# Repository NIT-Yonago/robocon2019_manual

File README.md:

# robocon2019_manual
# 
# Arduino/
## Controller
Wiiクラシックコントローラのデータをそのまま送信する

## hanging_system
ハンガーをかける機構のプログラム

Wiiから受信して，加工したデータを足回りに送る機能も持つ

## MD_Green
モータードライバ＊３

電磁弁駆動＊３

ロボット角度補正用ジャイロ

CAN通信（未実装）
# 
# KiCad/
## wii_controller
Controllerの基板

## AIR_SRV_SIX
hanging_systemの基板

## MD_2016_remake
MD_Greenの基板

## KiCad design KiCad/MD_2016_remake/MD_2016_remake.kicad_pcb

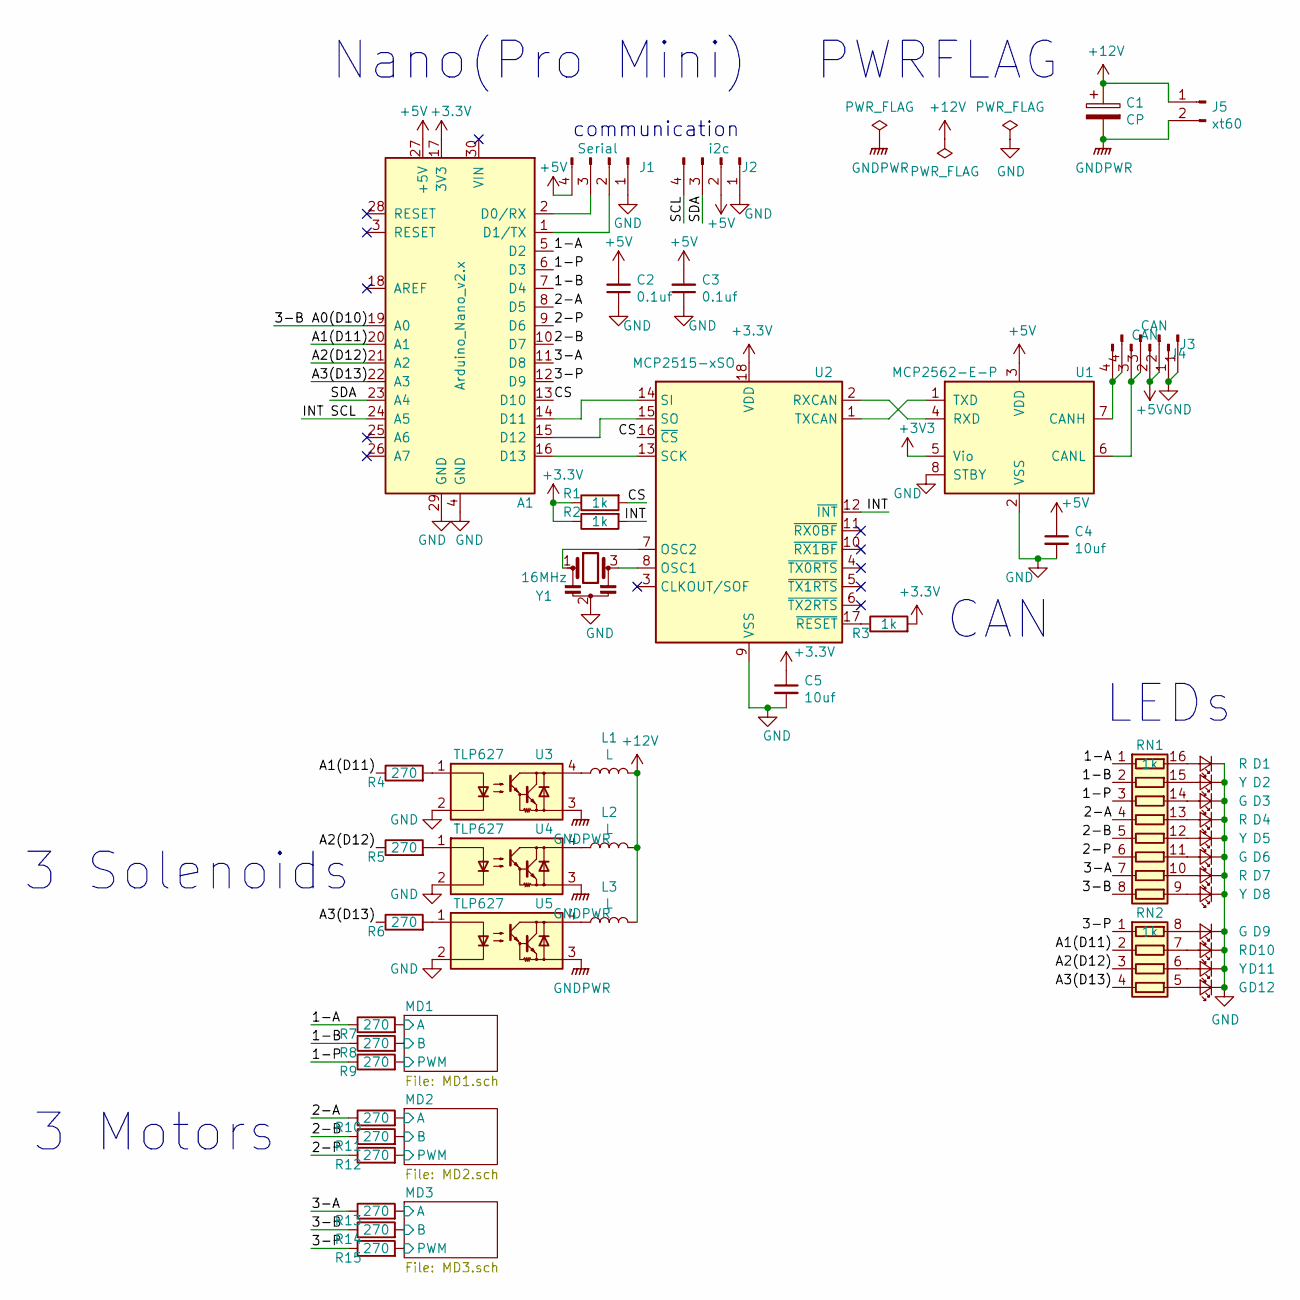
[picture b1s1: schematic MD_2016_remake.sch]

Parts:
A1: Arduino_Nano_v2.x; Arduino_Nano
C1: CP; CP_Radial_D10.0mm_P5.00mm
C2, C3: 0.1uf; C_0603_1608Metric
C4, C5: 10uf; C_0603_1608Metric
D1, D4, D7, D10: R; LED_0603_1608Metric
D2, D5, D8, D11: Y; LED_0603_1608Metric
D3, D6, D9, D12: G; LED_0603_1608Metric
J1: Serial; JST_PH_B4B-PH-K_1x04_P2.00mm_Vertical
J2: i2c; JST_PH_B4B-PH-K_1x04_P2.00mm_Vertical
J3, J4: CAN; JST_PH_B4B-PH-K_1x04_P2.00mm_Vertical
J5: xt60; XT60PT-M
L1, L2, L3: L; JST_PH_B2B-PH-K_1x02_P2.00mm_Vertical
R1, R2, R3: 1k; R_0603_1608Metric
R4, R5, R6, R7, R8, R9, R10, R11, R12, R13, R14, R15: 270; R_0603_1608Metric
RN1: 1k; R_Array_Convex_8x0602
RN2: 1k; R_Array_Convex_4x0603
U1: MCP2562-E-P; DIP-8_W7.62mm
U2: MCP2515-xSO; DIP-18_W7.62mm_Socket
U3, U4, U5: TLP627; DIP-4_W7.62mm
Y1: 16MHz; Resonator_muRata_CSTLSxxxX-3Pin_W5.5mm_H3.0mm

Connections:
+5V: A1.27 (+5V), C2.2, C3.2, C4.1, J1.4, J2.2, J3.2, J4.2, U1.3 (VDD)
+12V: C1.1, J5.1, L1.2, L2.2, L3.2; also elsewhere on the board
/1-A: A1.5 (D2), R7.1, RN1.1 (R1.1)
/1-B: A1.7 (D4), R8.1, RN1.2 (R2.1)
/1-P: A1.6 (D3), R9.1, RN1.3 (R3.1)
/2-A: A1.8 (D5), R10.1, RN1.4 (R4.1)
/2-B: A1.10 (D7), R11.1, RN1.5 (R5.1)
/2-P: A1.9 (D6), R12.1, RN1.6 (R6.1)
/3-A: A1.11 (D8), R13.1, RN1.7 (R7.1)
/3-B: A1.19 (A0), R14.1, RN1.8 (R8.1)
/3-P: A1.12 (D9), R15.1, RN2.1 (R1.1)
/A1(D11): A1.20 (A1), R4.1, RN2.2 (R2.1)
/A2(D12): A1.21 (A2), R5.1, RN2.3 (R3.1)
/A3(D13): A1.22 (A3), R6.1, RN2.4 (R4.1)
/CS: A1.13 (D10), R1.2, U2.16 (~CS)
/INT: A1.24 (A5), J2.4, R2.2, U2.12 (~INT)
/MD1/A: R7.2; also elsewhere on the board
/MD1/B: R8.2; also elsewhere on the board
/MD1/PWM: R9.2; also elsewhere on the board
/MD2/A: R10.2; also elsewhere on the board
/MD2/B: R11.2; also elsewhere on the board
/MD2/PWM: R12.2; also elsewhere on the board
/MD3/A: R13.2; also elsewhere on the board
/MD3/B: R14.2; also elsewhere on the board
/MD3/PWM: R15.2; also elsewhere on the board
/SDA: A1.23 (A4), J2.3
GND: A1.4 (GND), A1.29 (GND), C2.1, C3.1, C4.2, C5.2, D1.1 (K), D2.1 (K), D3.1 (K), D4.1 (K), D5.1 (K), D6.1 (K), D7.1 (K), D8.1 (K), D9.1 (K), D10.1 (K), D11.1 (K), D12.1 (K), J1.1, J2.1, J3.1, J4.1, U1.2 (VSS), U1.8 (STBY), U2.9 (VSS), U3.2, U4.2, U5.2, Y1.2; also elsewhere on the board
GNDPWR: C1.2, J5.2, U3.3, U4.3, U5.3; also elsewhere on the board
unnamed: A1.1 (D1/TX), J1.2
unnamed: A1.2 (D0/RX), J1.3
unnamed: A1.14 (D11), U2.14 (SI)
unnamed: A1.15 (D12), U2.15 (SO)
unnamed: A1.16 (D13), U2.13 (SCK)
unnamed: D1.2 (A), RN1.16 (R1.2)
unnamed: D2.2 (A), RN1.15 (R2.2)
unnamed: D3.2 (A), RN1.14 (R3.2)
unnamed: D4.2 (A), RN1.13 (R4.2)
unnamed: D5.2 (A), RN1.12 (R5.2)
unnamed: D6.2 (A), RN1.11 (R6.2)
unnamed: D7.2 (A), RN1.10 (R7.2)
unnamed: D8.2 (A), RN1.9 (R8.2)
unnamed: D9.2 (A), RN2.8 (R1.2)
unnamed: D10.2 (A), RN2.7 (R2.2)
unnamed: D11.2 (A), RN2.6 (R3.2)
unnamed: D12.2 (A), RN2.5 (R4.2)
unnamed: J3.3, J4.3, U1.6 (CANL)
unnamed: J3.4, J4.4, U1.7 (CANH)
unnamed: L1.1, U3.4
unnamed: L2.1, U4.4
unnamed: L3.1, U5.4
unnamed: R3.1, U2.17 (~RESET)
unnamed: R4.2, U3.1
unnamed: R5.2, U4.1
unnamed: R6.2, U5.1
unnamed: U1.1 (TXD), U2.1 (TXCAN)
unnamed: U1.4 (RXD), U2.2 (RXCAN)
unnamed: U2.7 (OSC2), Y1.1
unnamed: U2.8 (OSC1), Y1.3

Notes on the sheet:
3 Motors
CAN
Nano(Pro Mini)
PWRFLAG
communication
LEDs
3 Solenoids

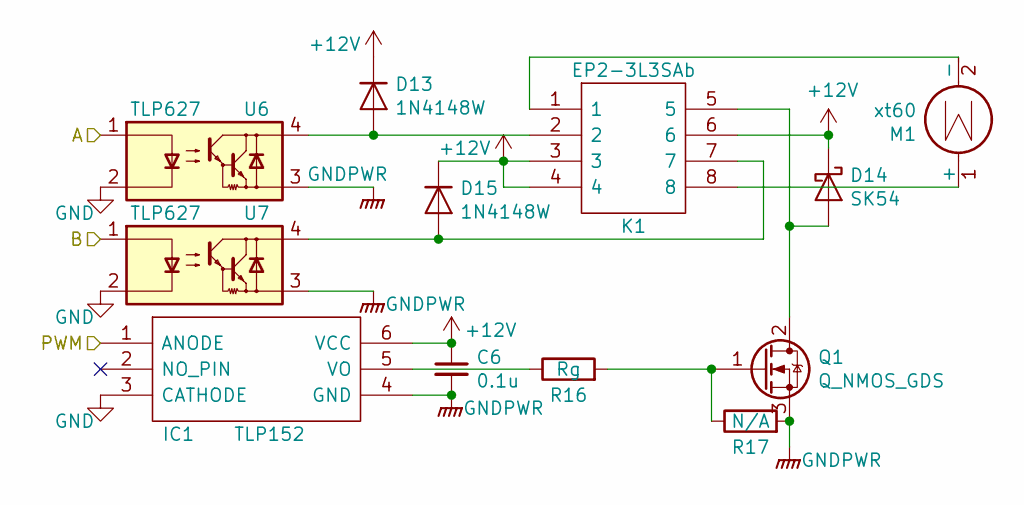
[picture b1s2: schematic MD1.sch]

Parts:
C6: 0.1u; C_0603_1608Metric
D13, D15: 1N4148W; D_SOD-123
D14: SK54; D_SMC
IC1: TLP152; SO-5_4.4x3.6mm_P1.27mm; Manufacturer_Part_Number TLP152(E(T
K1: EP2-3L3SAb; EP2_H-BRIDGE; Manufacturer_Part_Number EP2-3L3SAb
M1: xt60; XT60PT-F
Q1: Q_NMOS_GDS; TO-247-3_Vertical
R16: Rg; R_0603_1608Metric_Pad1.05x0.95mm_HandSolder
R17: N/A; R_0603_1608Metric_Pad1.05x0.95mm_HandSolder
U6, U7: TLP627; DIP-4_W7.62mm

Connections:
+12V: C6.1, D13.1 (K), D14.1 (K), D15.1 (K), IC1.6 (VCC), K1.3, K1.4, K1.6; also elsewhere on the board
/MD1/A: U6.1; also elsewhere on the board
/MD1/B: U7.1; also elsewhere on the board
/MD1/PWM: IC1.1 (ANODE); also elsewhere on the board
GND: IC1.3 (CATHODE), U6.2, U7.2; also elsewhere on the board
GNDPWR: C6.2, IC1.4 (GND), Q1.3 (S), R17.2, U6.3, U7.3; also elsewhere on the board
unnamed: D13.2 (A), K1.2, U6.4
unnamed: D14.2 (A), K1.5, Q1.2 (D)
unnamed: D15.2 (A), K1.7, U7.4
unnamed: IC1.5 (VO), R16.1
unnamed: K1.1, M1.2 (-)
unnamed: K1.8, M1.1 (+)
unnamed: Q1.1 (G), R16.2, R17.1

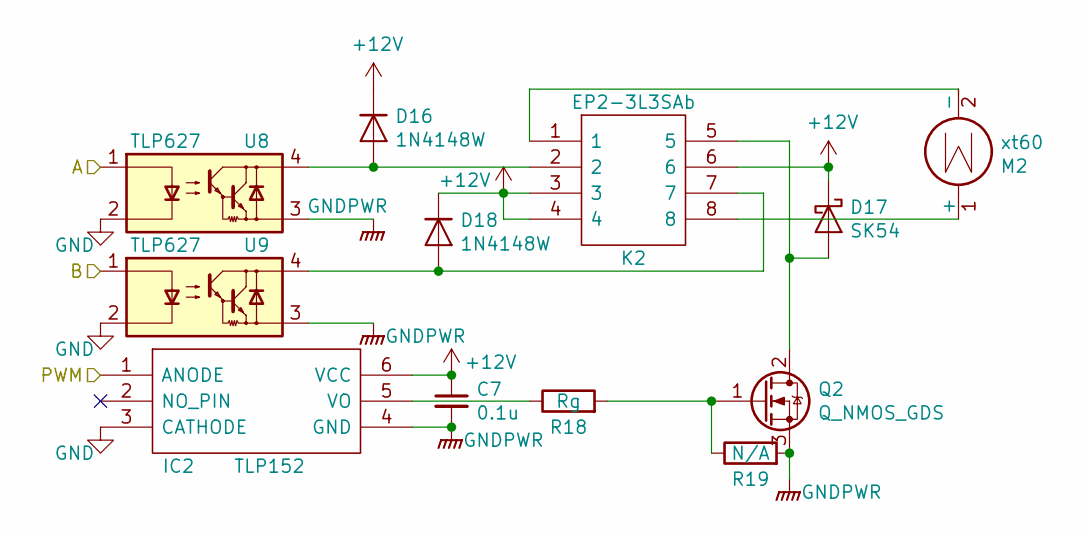
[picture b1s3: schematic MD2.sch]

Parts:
C7: 0.1u; C_0603_1608Metric
D16, D18: 1N4148W; D_SOD-123
D17: SK54; D_SMC
IC2: TLP152; SO-5_4.4x3.6mm_P1.27mm; Manufacturer_Part_Number TLP152(E(T
K2: EP2-3L3SAb; EP2_H-BRIDGE; Manufacturer_Part_Number EP2-3L3SAb
M2: xt60; XT60PT-F
Q2: Q_NMOS_GDS; TO-247-3_Vertical
R18: Rg; R_0603_1608Metric_Pad1.05x0.95mm_HandSolder
R19: N/A; R_0603_1608Metric_Pad1.05x0.95mm_HandSolder
U8, U9: TLP627; DIP-4_W7.62mm

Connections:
+12V: C7.1, D16.1 (K), D17.1 (K), D18.1 (K), IC2.6 (VCC), K2.3, K2.4, K2.6; also elsewhere on the board
/MD2/A: U8.1; also elsewhere on the board
/MD2/B: U9.1; also elsewhere on the board
/MD2/PWM: IC2.1 (ANODE); also elsewhere on the board
GND: IC2.3 (CATHODE), U8.2, U9.2; also elsewhere on the board
GNDPWR: C7.2, IC2.4 (GND), Q2.3 (S), R19.2, U8.3, U9.3; also elsewhere on the board
unnamed: D16.2 (A), K2.2, U8.4
unnamed: D17.2 (A), K2.5, Q2.2 (D)
unnamed: D18.2 (A), K2.7, U9.4
unnamed: IC2.5 (VO), R18.1
unnamed: K2.1, M2.2 (-)
unnamed: K2.8, M2.1 (+)
unnamed: Q2.1 (G), R18.2, R19.1

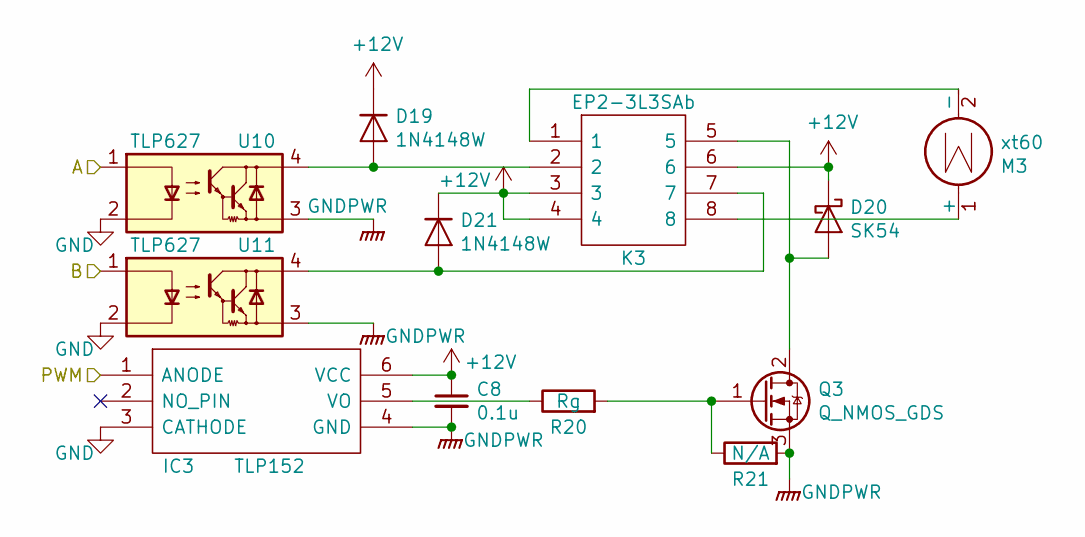
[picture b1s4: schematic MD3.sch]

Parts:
C8: 0.1u; C_0603_1608Metric
D19, D21: 1N4148W; D_SOD-123
D20: SK54; D_SMC
IC3: TLP152; SO-5_4.4x3.6mm_P1.27mm; Manufacturer_Part_Number TLP152(E(T
K3: EP2-3L3SAb; EP2_H-BRIDGE; Manufacturer_Part_Number EP2-3L3SAb
M3: xt60; XT60PT-F
Q3: Q_NMOS_GDS; TO-247-3_Vertical
R20: Rg; R_0603_1608Metric_Pad1.05x0.95mm_HandSolder
R21: N/A; R_0603_1608Metric_Pad1.05x0.95mm_HandSolder
U10, U11: TLP627; DIP-4_W7.62mm

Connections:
+12V: C8.1, D19.1 (K), D20.1 (K), D21.1 (K), IC3.6 (VCC), K3.3, K3.4, K3.6; also elsewhere on the board
/MD3/A: U10.1; also elsewhere on the board
/MD3/B: U11.1; also elsewhere on the board
/MD3/PWM: IC3.1 (ANODE); also elsewhere on the board
GND: IC3.3 (CATHODE), U10.2, U11.2; also elsewhere on the board
GNDPWR: C8.2, IC3.4 (GND), Q3.3 (S), R21.2, U10.3, U11.3; also elsewhere on the board
unnamed: D19.2 (A), K3.2, U10.4
unnamed: D20.2 (A), K3.5, Q3.2 (D)
unnamed: D21.2 (A), K3.7, U11.4
unnamed: IC3.5 (VO), R20.1
unnamed: K3.1, M3.2 (-)
unnamed: K3.8, M3.1 (+)
unnamed: Q3.1 (G), R20.2, R21.1

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
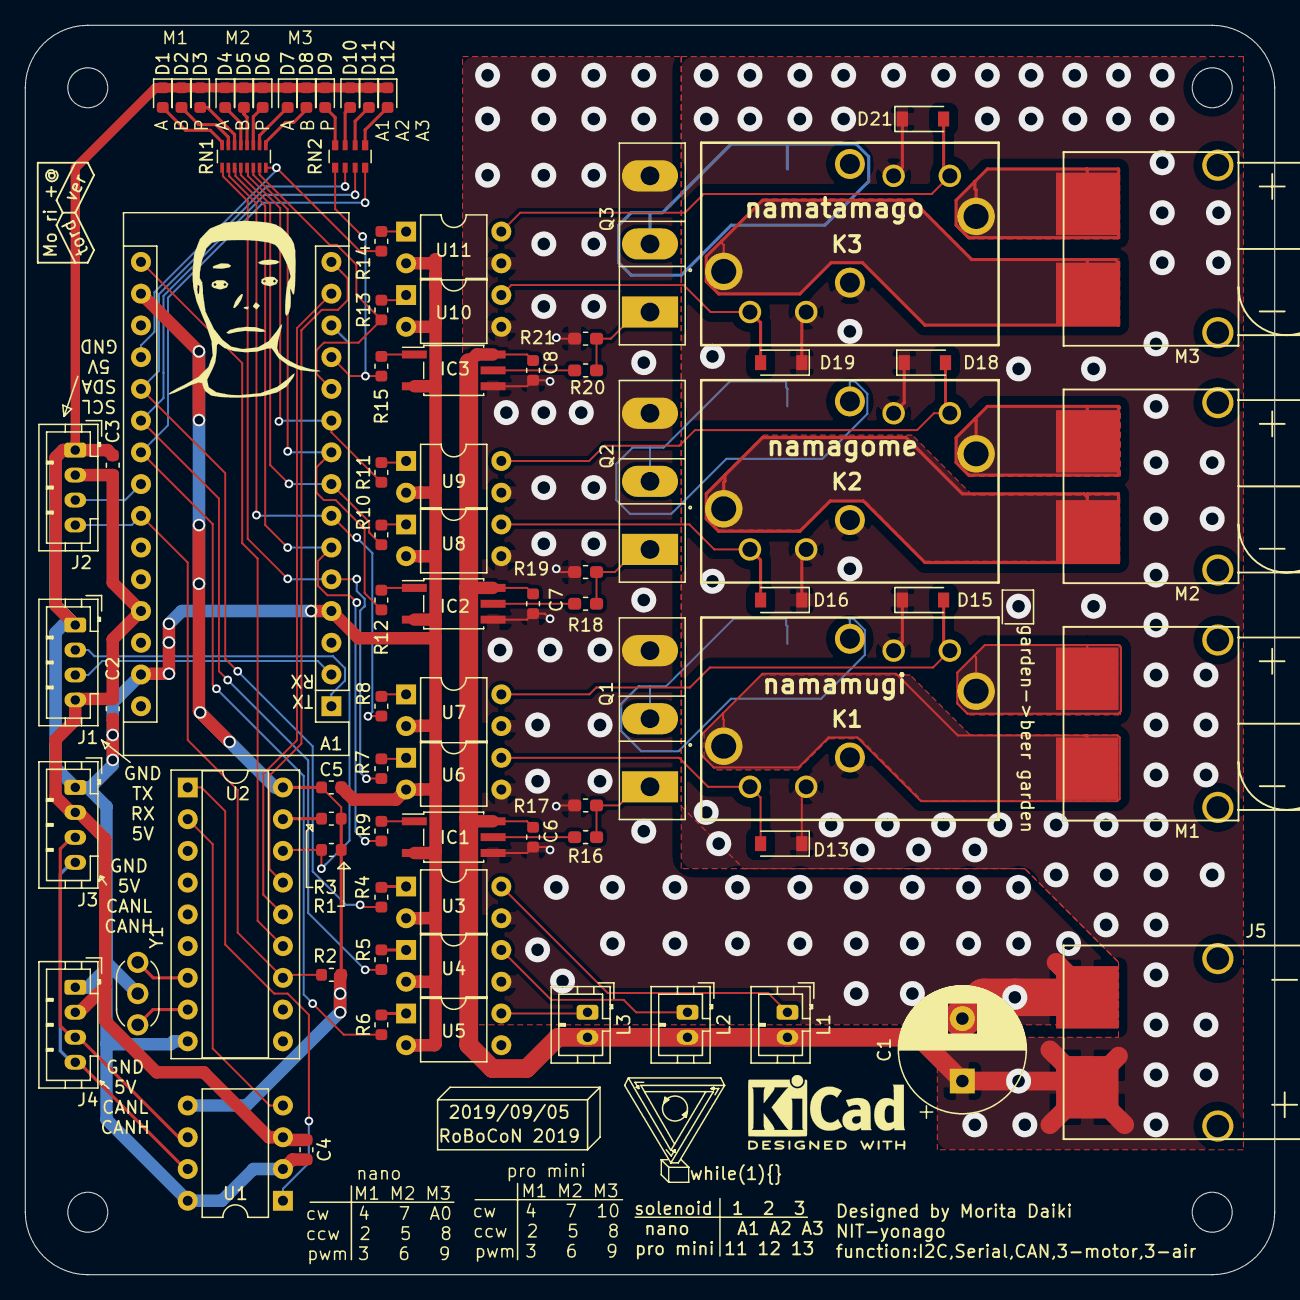
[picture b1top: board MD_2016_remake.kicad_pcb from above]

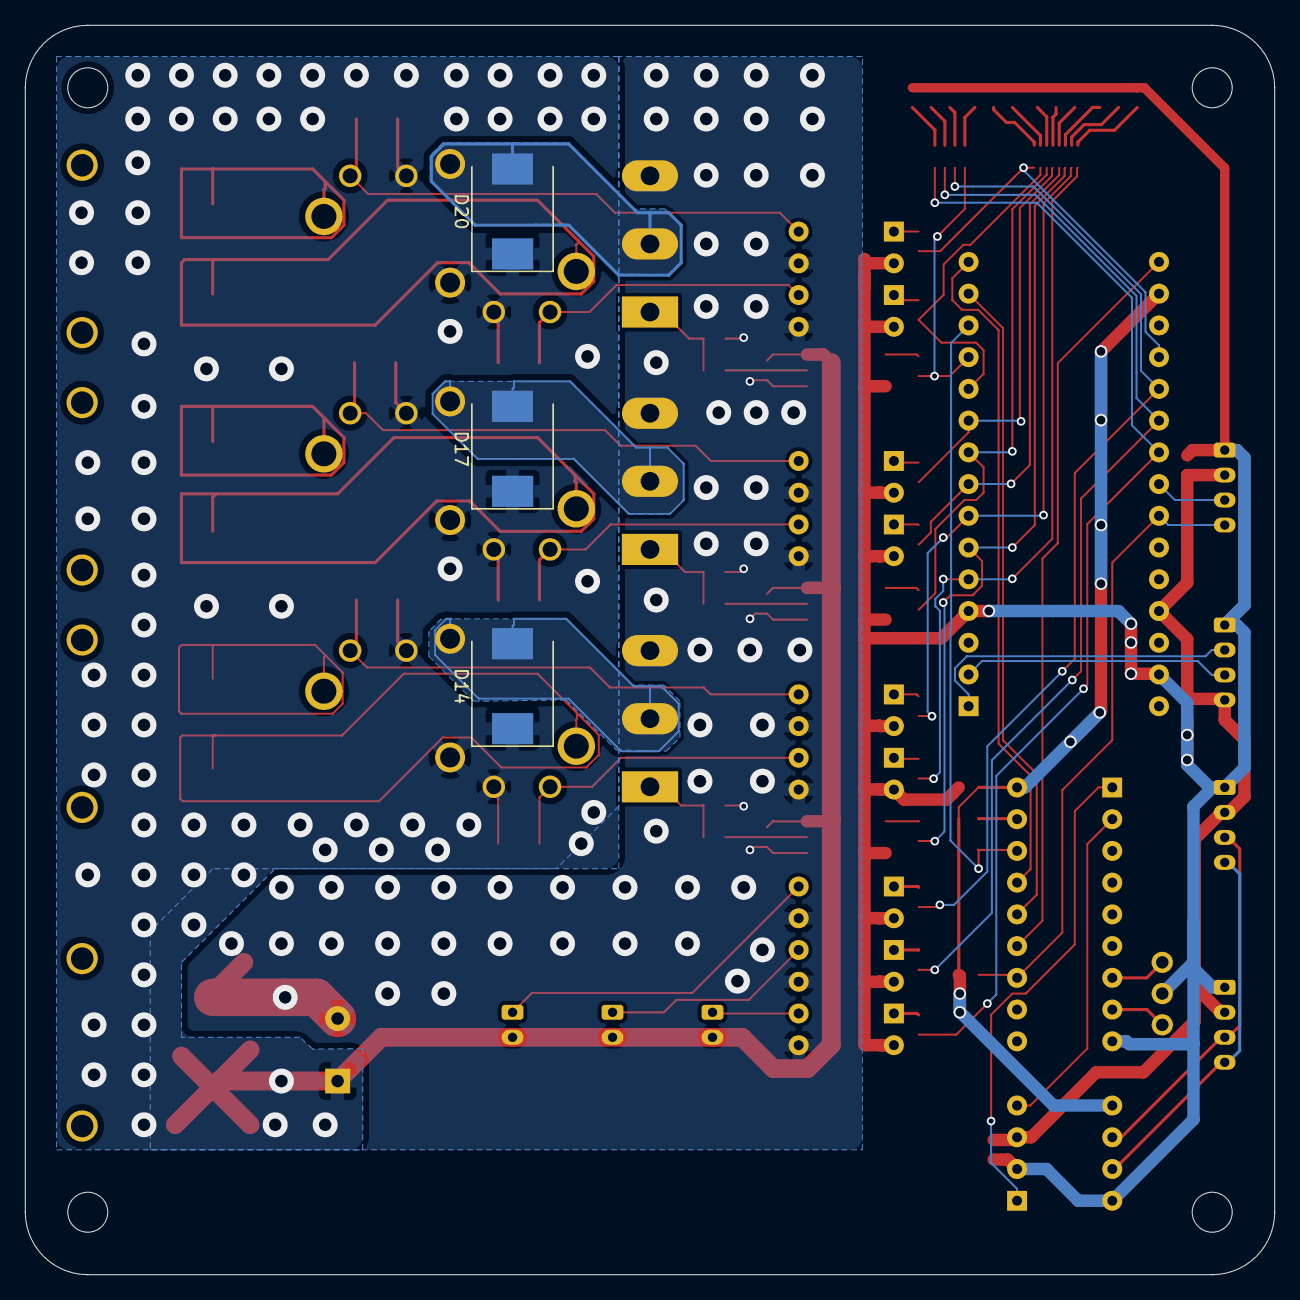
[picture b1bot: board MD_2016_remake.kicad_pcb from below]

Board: 2 copper layers, 100.0 x 100.0 mm, 85 parts (3 on the bottom side), 80 nets.

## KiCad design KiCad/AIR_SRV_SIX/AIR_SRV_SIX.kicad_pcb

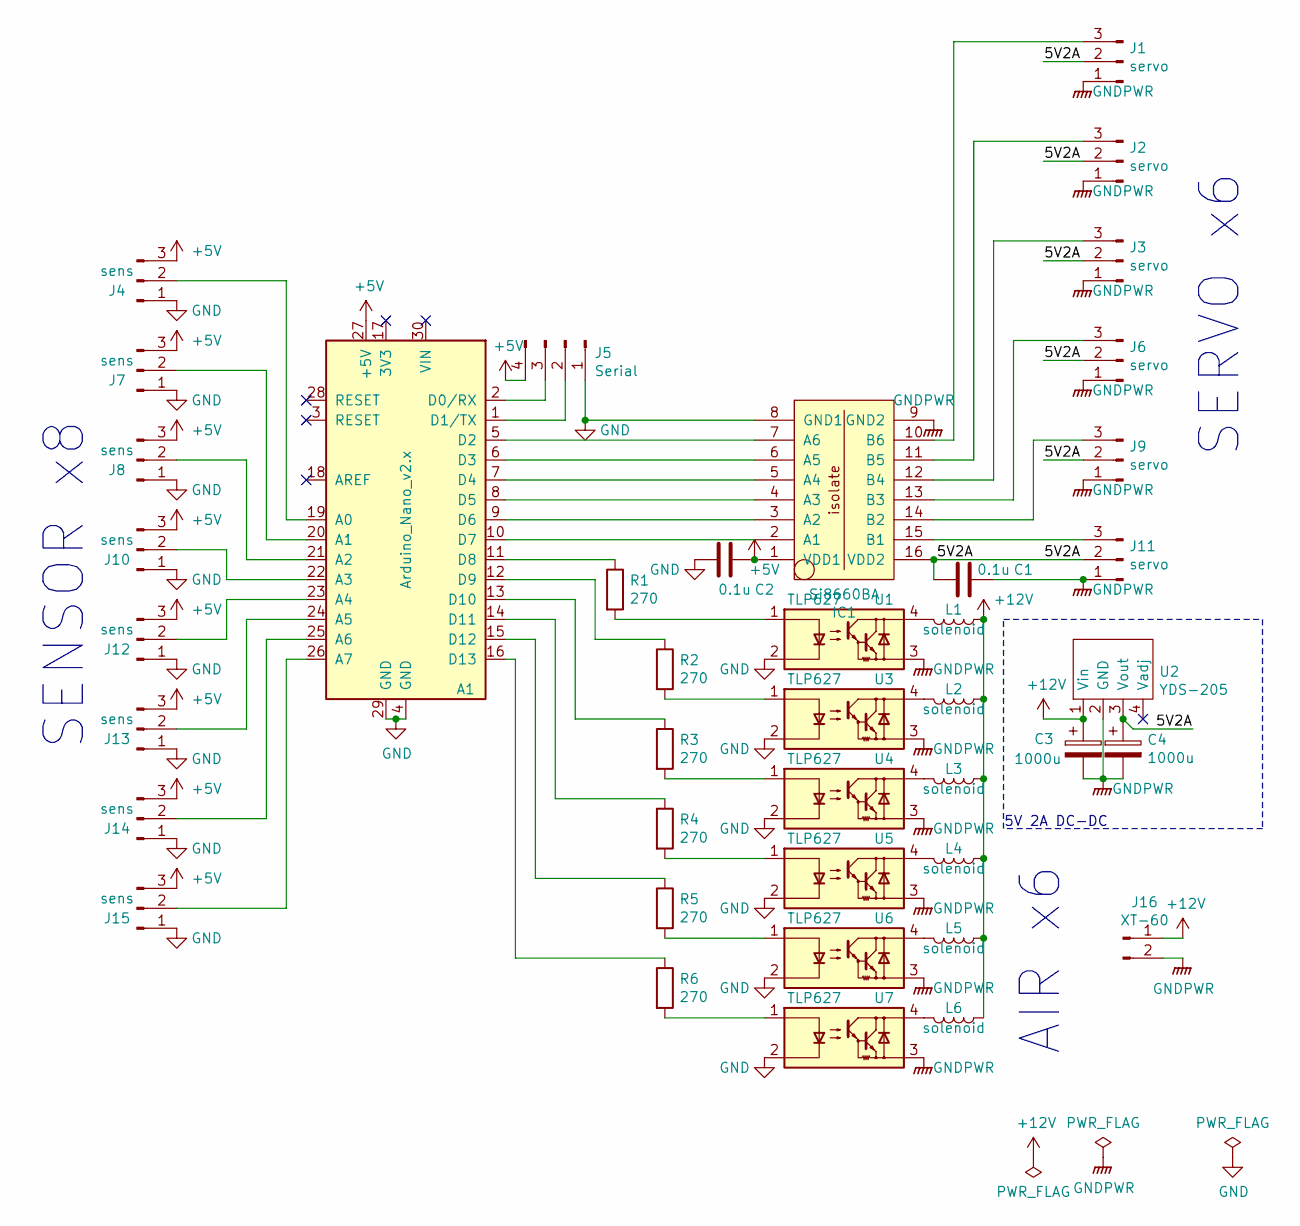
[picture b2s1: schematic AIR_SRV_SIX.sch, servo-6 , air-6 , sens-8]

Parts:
A1: Arduino_Nano_v2.x; Arduino_Nano
C1, C2: 0.1u; C_0603_1608Metric
C3, C4: 1000u; CP_Radial_D10.0mm_P5.00mm
IC1: Si8660BA; SOIC-16_3.9x9.9mm_P1.27mm
J1, J2, J3, J6, J9, J11: servo; JST_PH_B3B-PH-K_1x03_P2.00mm_Vertical
J4, J7, J8, J10, J12, J13, J14, J15: sens; JST_PH_B3B-PH-K_1x03_P2.00mm_Vertical
J5: Serial; JST_XH_S4B-XH-A-1_1x04_P2.50mm_Horizontal
J16: XT-60; XT60PT-M
L1, L2, L3, L4, L5, L6: solenoid; JST_PH_B2B-PH-K_1x02_P2.00mm_Vertical
R1, R2, R3, R4, R5, R6: 270; R_0603_1608Metric
U1, U3, U4, U5, U6, U7: TLP627; DIP-4_W7.62mm
U2: YDS-205

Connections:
+5V: A1.27 (+5V), C2.1, IC1.1 (VDD1), J4.3, J5.4, J7.3, J8.3, J10.3, J12.3, J13.3, J14.3, J15.3
+12V: C3.1, J16.1, L1.1, L2.1, L3.1, L4.1, L5.1, L6.1, U2.1 (Vin)
/5V2A: C1.1, C4.1, IC1.16 (VDD2), J1.2, J2.2, J3.2, J6.2, J9.2, J11.2, U2.3 (Vout)
GND: A1.4 (GND), A1.29 (GND), C2.2, IC1.8 (GND1), J4.1, J5.1, J7.1, J8.1, J10.1, J12.1, J13.1, J14.1, J15.1, U1.2, U3.2, U4.2, U5.2, U6.2, U7.2
GNDPWR: C1.2, C3.2, C4.2, IC1.9 (GND2), J1.1, J2.1, J3.1, J6.1, J9.1, J11.1, J16.2, U1.3, U2.2 (GND), U3.3, U4.3, U5.3, U6.3, U7.3
unnamed: A1.1 (D1/TX), J5.2
unnamed: A1.2 (D0/RX), J5.3
unnamed: A1.5 (D2), IC1.7 (A6)
unnamed: A1.6 (D3), IC1.6 (A5)
unnamed: A1.7 (D4), IC1.5 (A4)
unnamed: A1.8 (D5), IC1.4 (A3)
unnamed: A1.9 (D6), IC1.3 (A2)
unnamed: A1.10 (D7), IC1.2 (A1)
unnamed: A1.11 (D8), R1.1
unnamed: A1.12 (D9), R2.1
unnamed: A1.13 (D10), R3.1
unnamed: A1.14 (D11), R4.1
unnamed: A1.15 (D12), R5.1
unnamed: A1.16 (D13), R6.1
unnamed: A1.19 (A0), J4.2
unnamed: A1.20 (A1), J7.2
unnamed: A1.21 (A2), J8.2
unnamed: A1.22 (A3), J10.2
unnamed: A1.23 (A4), J12.2
unnamed: A1.24 (A5), J13.2
unnamed: A1.25 (A6), J14.2
unnamed: A1.26 (A7), J15.2
unnamed: IC1.10 (B6), J1.3
unnamed: IC1.11 (B5), J2.3
unnamed: IC1.12 (B4), J3.3
unnamed: IC1.13 (B3), J6.3
unnamed: IC1.14 (B2), J9.3
unnamed: IC1.15 (B1), J11.3
unnamed: L1.2, U1.4
unnamed: L2.2, U3.4
unnamed: L3.2, U4.4
unnamed: L4.2, U5.4
unnamed: L5.2, U6.4
unnamed: L6.2, U7.4
unnamed: R1.2, U1.1
unnamed: R2.2, U3.1
unnamed: R3.2, U4.1
unnamed: R4.2, U5.1
unnamed: R5.2, U6.1
unnamed: R6.2, U7.1

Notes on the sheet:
5V 2A DC-DC
SERVO x6
AIR x6
SENSOR x8

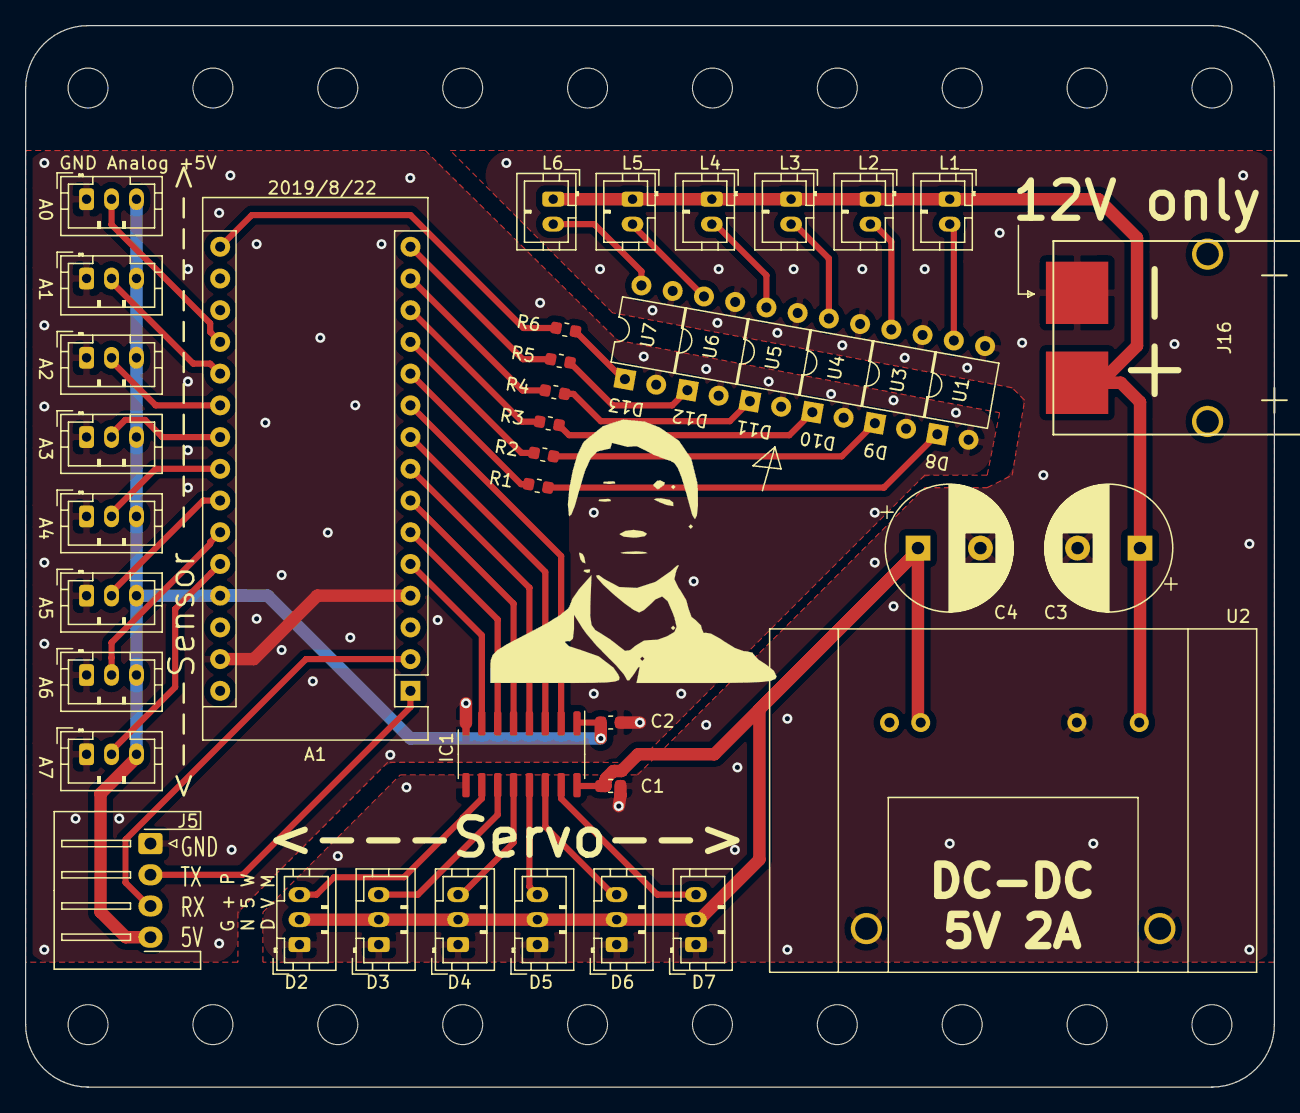
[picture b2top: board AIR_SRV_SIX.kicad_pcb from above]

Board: 2 copper layers, 100.0 x 85.0 mm, 41 parts (0 on the bottom side), 45 nets.

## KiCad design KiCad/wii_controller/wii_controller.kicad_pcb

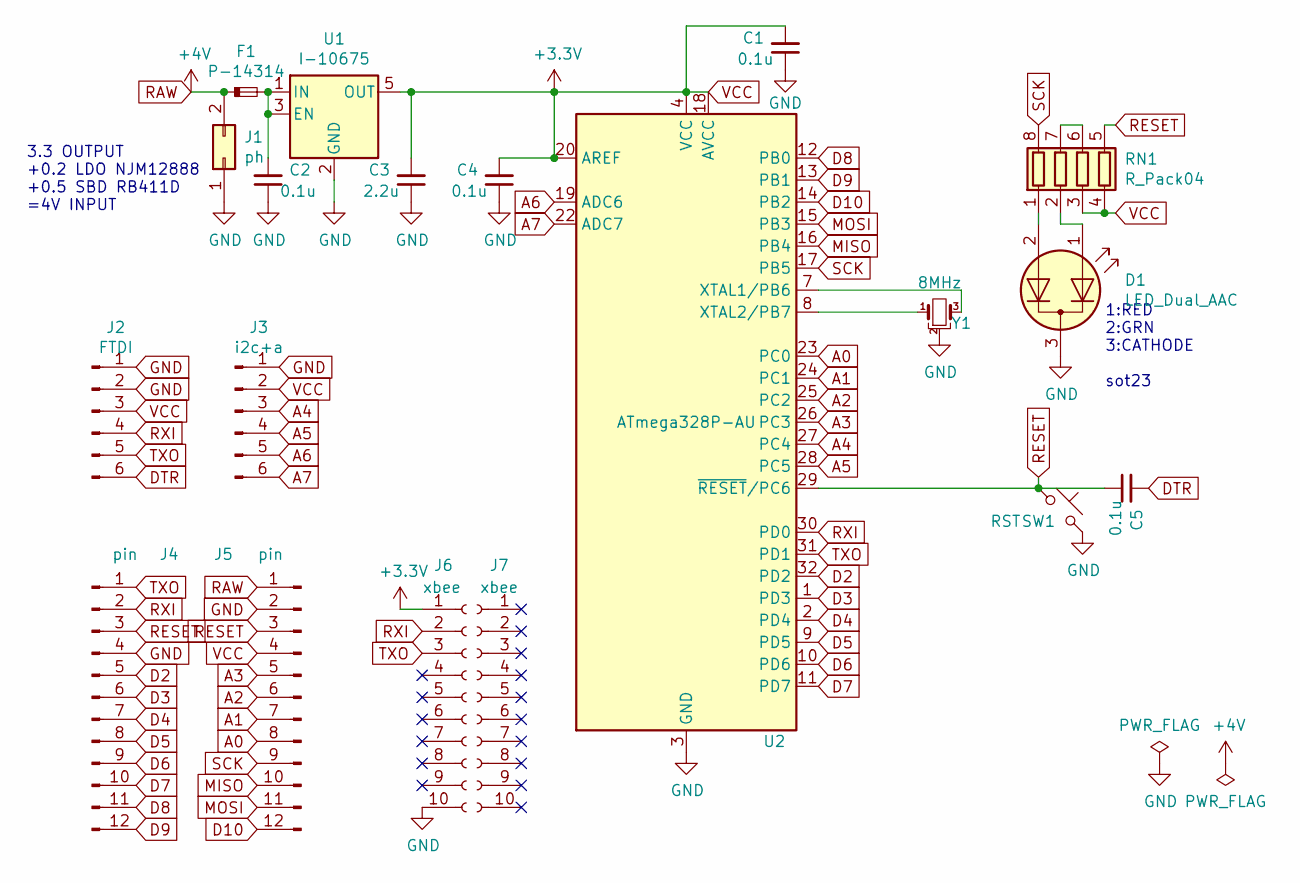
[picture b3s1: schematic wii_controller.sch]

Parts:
C1, C2, C4, C5: 0.1u; C_0402_1005Metric
C3: 2.2u; C_0402_1005Metric
D1: LED_Dual_AAC; SOT-23
F1: P-14314; Fuse_0603_1608Metric
J1: ph; JST_PH_S2B-PH-K_1x02_P2.00mm_Horizontal
J2: FTDI; PinHeader_1x06_P2.54mm_Vertical
J3: i2c+a; PinHeader_1x06_P2.54mm_Horizontal
J4, J5: pin; PinHeader_1x12_P2.54mm_Vertical
J6, J7: xbee; PinHeader_1x10_P2.00mm_Vertical
RN1: R_Pack04; R_Array_Concave_4x0603
SW1: RST; ESE22MH4XDK
U1: I-10675; SOT-23-5
U2: ATmega328P-AU; TQFP-32_7x7mm_P0.8mm
Y1: 8MHz; Resonator_muRata_CSTLSxxxG-3Pin_W8.0mm_H3.0mm

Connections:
A0: J5.8, U2.23 (PC0)
A1: J5.7, U2.24 (PC1)
A2: J5.6, U2.25 (PC2)
A3: J5.5, U2.26 (PC3)
A4: J3.3, U2.27 (PC4)
A5: J3.4, U2.28 (PC5)
A6: J3.5, U2.19 (ADC6)
A7: J3.6, U2.22 (ADC7)
D2: J4.5, U2.32 (PD2)
D3: J4.6, U2.1 (PD3)
D4: J4.7, U2.2 (PD4)
D5: J4.8, U2.9 (PD5)
D6: J4.9, U2.10 (PD6)
D7: J4.10, U2.11 (PD7)
D8: J4.11, U2.12 (PB0)
D9: J4.12, U2.13 (PB1)
D10: J5.12, U2.14 (PB2)
DTR: C5.2, J2.6
GND: C1.1, C2.1, C3.1, C4.1, D1.3 (K), J1.1, J2.1, J2.2, J3.1, J4.4, J5.2, J6.10, SW1.2, U1.2 (GND), U2.3 (GND), U2.5 (GND), U2.21 (GND), Y1.2
MISO: J5.10, U2.16 (PB4)
MOSI: J5.11, U2.15 (PB3)
unnamed: C2.2, F1.2, U1.1 (IN), U1.3 (EN)
unnamed: D1.1 (A1), RN1.2 (R2.1)
unnamed: D1.2 (A2), RN1.1 (R1.1)
unnamed: RN1.6 (R3.2), RN1.7 (R2.2)
unnamed: U2.7 (XTAL1/PB6), Y1.3
unnamed: U2.8 (XTAL2/PB7), Y1.1
RAW: F1.1, J1.2, J5.1
RESET: C5.1, J4.3, J5.3, RN1.5 (R4.2), SW1.1, U2.29 (~RESET~/PC6)
RXI: J2.4, J4.2, J6.2, U2.30 (PD0)
SCK: J5.9, RN1.8 (R1.2), U2.17 (PB5)
TXO: J2.5, J4.1, J6.3, U2.31 (PD1)
VCC: C1.2, C3.2, C4.2, J2.3, J3.2, J5.4, J6.1, RN1.3 (R3.1), RN1.4 (R4.1), U1.5 (OUT), U2.4 (VCC), U2.6 (VCC), U2.18 (AVCC), U2.20 (AREF)

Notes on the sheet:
3.3 OUTPUT +0.2 LDO NJM12888 +0.5 SBD RB411D =4V INPUT
1:RED 2:GRN 3:CATHODE sot23

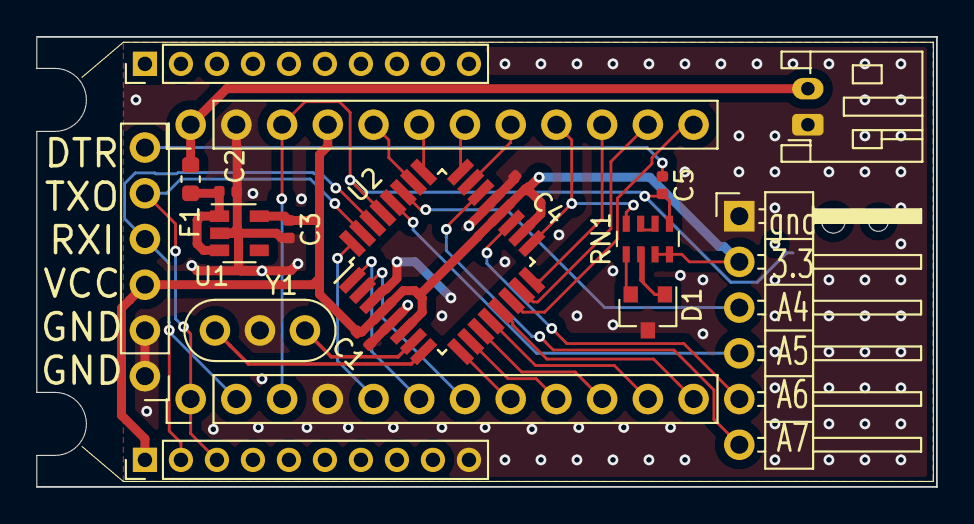
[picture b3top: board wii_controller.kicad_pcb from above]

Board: 2 copper layers, 50.0 x 25.0 mm, 19 parts (1 on the bottom side), 33 nets.

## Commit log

2019-10-13 rotation direction change
2019-10-13 yamamotokomitto
2019-10-13 通信関係調整
2019-10-13 コメント修正
2019-10-13 README かいた
2019-10-13 画像追加
